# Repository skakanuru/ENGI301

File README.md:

<h1> ENGI301 </h1>
Repository for ENGI301 course work

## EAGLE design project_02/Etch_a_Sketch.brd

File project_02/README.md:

Project 2 for ENGI 301

Full PCB Design and Files for Etch-A-Sketch Design

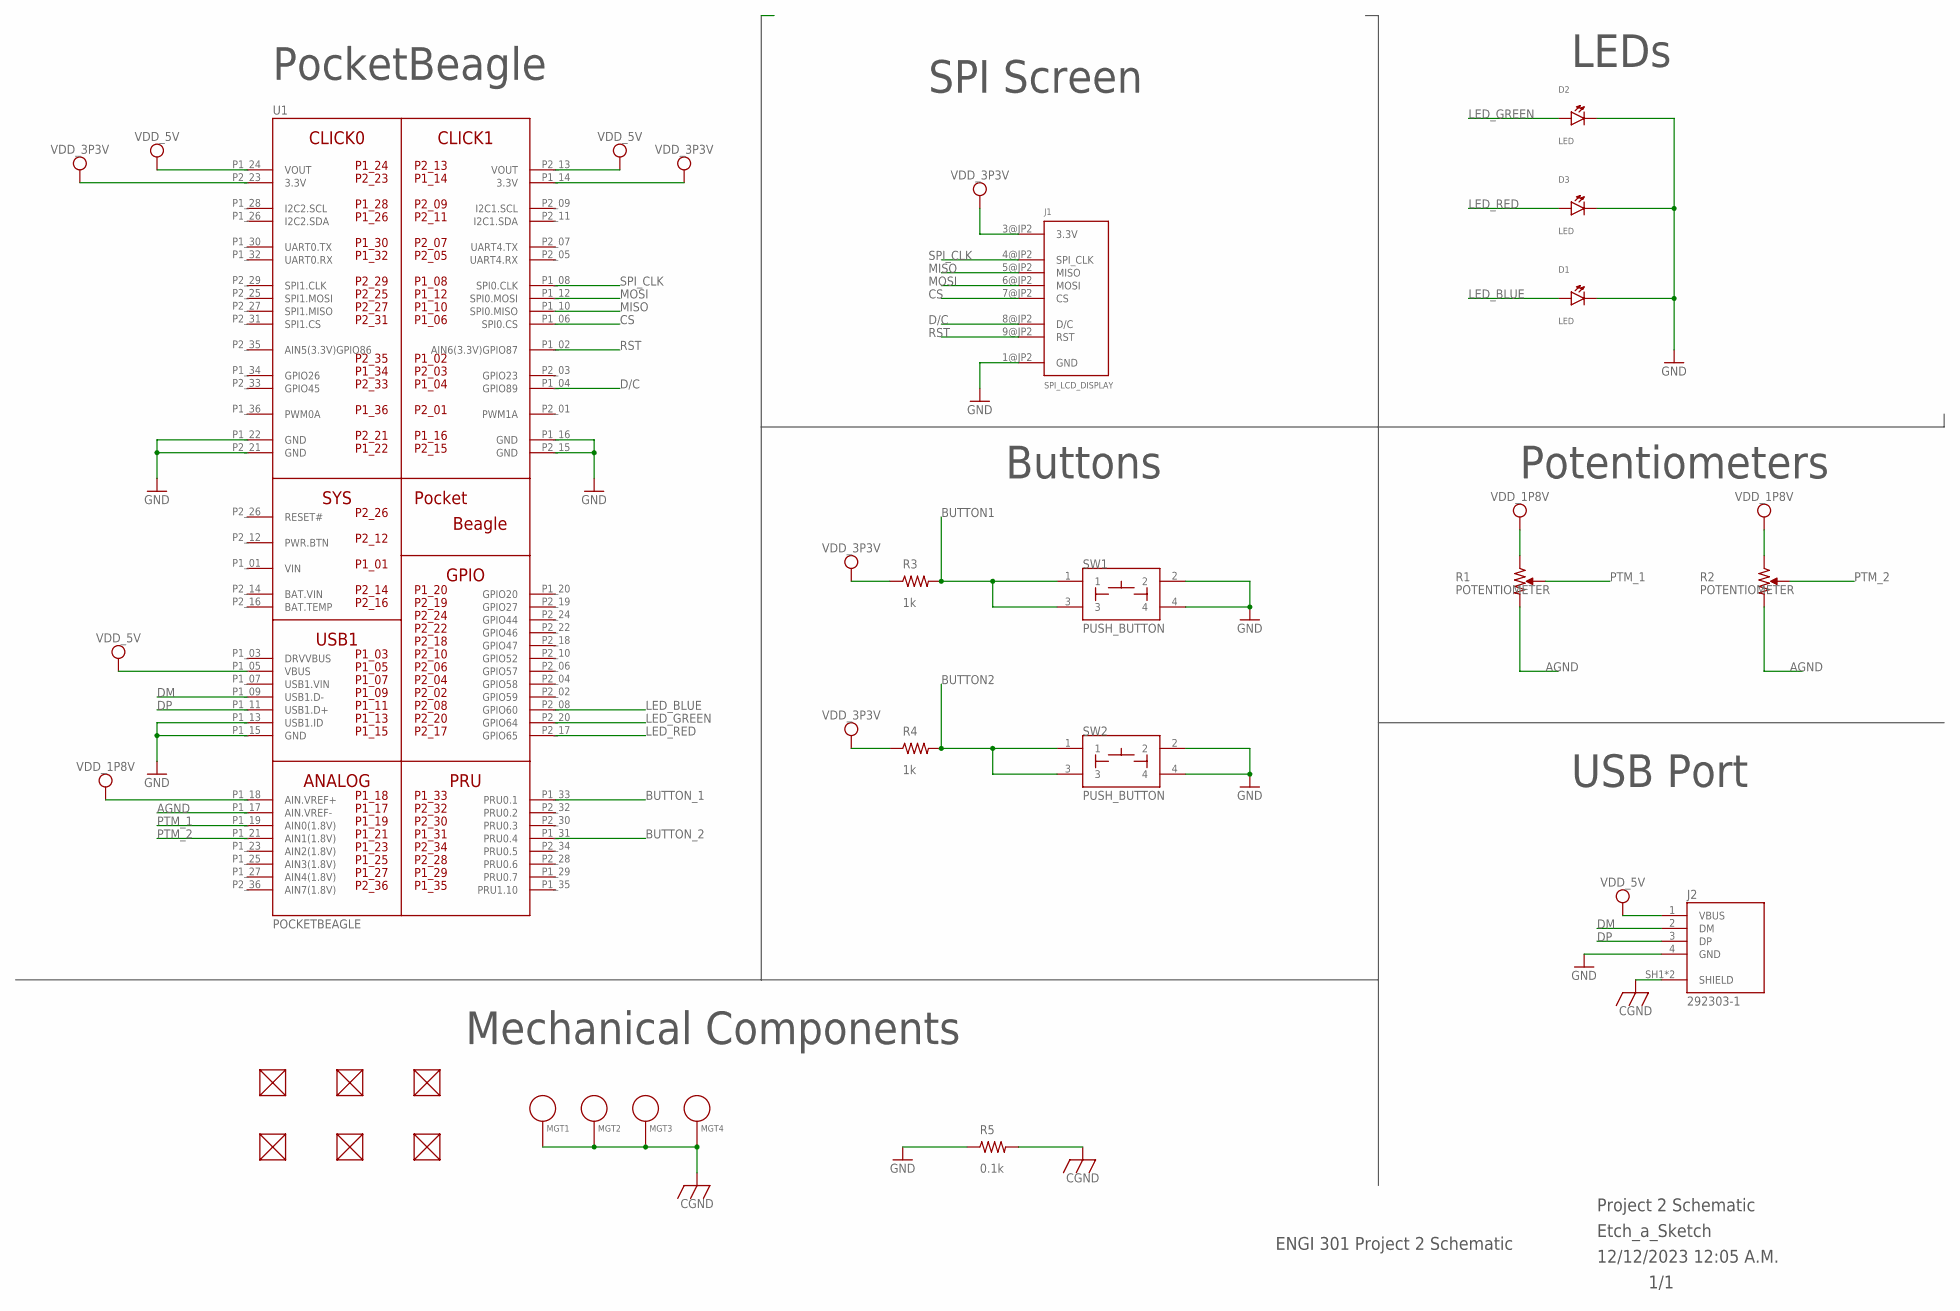
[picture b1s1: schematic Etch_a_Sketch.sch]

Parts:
D1, D2, D3: LED; EIA-STD
FUD1, FUD2, FUD3, FUD4, FUD5, FUD6: FIDUCIAL; FIDUCIAL_40MIL
J1: SPI_LCD_DISPLAY
J2: 292303-1; TE_292303-1
MGT1, MGT2, MGT3, MGT4: MOUNTING_HOLE
R1, R2: POTENTIOMETER; POT-PO90S
R3, R4: 1k; R0603
R5: 0.1k; R0603
SW1, SW2: PUSH_BUTTON; BUTTON_12.5MM
U1: POCKETBEAGLE

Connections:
AGND: R1.CW, R2.CW, U1.P1_17 (AIN.VREF-)
BAT.VIN: U1.P2_14 (BAT.VIN)
BUTTON1: R3.2, SW1.1, SW1.3
BUTTON2: R4.2, SW2.1, SW2.3
BUTTON_1: U1.P1_33 (PRU0.1)
BUTTON_2: U1.P1_31 (PRU0.4)
CGND: J2.SH1 (SHIELD), J2.SH2 (SHIELD), MGT1.P$1, MGT2.P$1, MGT3.P$1, MGT4.P$1, R5.2
CS: J1.7@JP2 (CS), U1.P1_06 (SPI0.CS)
D/C: J1.8@JP2 (D/C), U1.P1_04 (GPIO89)
DM: J2.2 (DM), U1.P1_09 (USB1.D-)
DP: J2.3 (DP), U1.P1_11 (USB1.D+)
GND: D1.CATHODE, D2.CATHODE, D3.CATHODE, J1.1@JP2 (GND), J2.4 (GND), R5.1, SW1.2, SW1.4, SW2.2, SW2.4, U1.P1_13 (USB1.ID), U1.P1_15 (GND), U1.P1_16 (GND), U1.P1_22 (GND), U1.P2_15 (GND), U1.P2_21 (GND)
LED_BLUE: D1.ANODE, U1.P2_08 (GPIO60)
LED_GREEN: D2.ANODE, U1.P2_20 (GPIO64)
LED_RED: D3.ANODE, U1.P2_17 (GPIO65)
MISO: J1.5@JP2 (MISO), U1.P1_10 (SPI0.MISO)
MOSI: J1.6@JP2 (MOSI), U1.P1_12 (SPI0.MOSI)
PTM_1: R1.S, U1.P1_19 (AIN0(1.8V))
PTM_2: R2.S, U1.P1_21 (AIN1(1.8V))
RST: J1.9@JP2 (RST), U1.P1_02 (AIN6(3.3V)GPIO87)
SPI_CLK: J1.4@JP2 (SPI_CLK), U1.P1_08 (SPI0.CLK)
VDD_1P8V: R1.CCW, R2.CCW, U1.P1_18 (AIN.VREF+)
VDD_3P3V: J1.3@JP2 (3.3V), R3.1, R4.1, U1.P1_14 (3.3V), U1.P2_23 (3.3V)
VDD_5V: J2.1 (VBUS), U1.P1_05 (VBUS), U1.P1_24 (VOUT), U1.P2_13 (VOUT)
VIN: U1.P1_01 (VIN)

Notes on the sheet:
Buttons
Potentiometers
LEDs
USB Port
Mechanical Components
SPI Screen
PocketBeagle
ENGI 301 Project 2 Schematic
Project 2 Schematic
1/1
Etch_a_Sketch
12/12/2023 12:05 A.M.

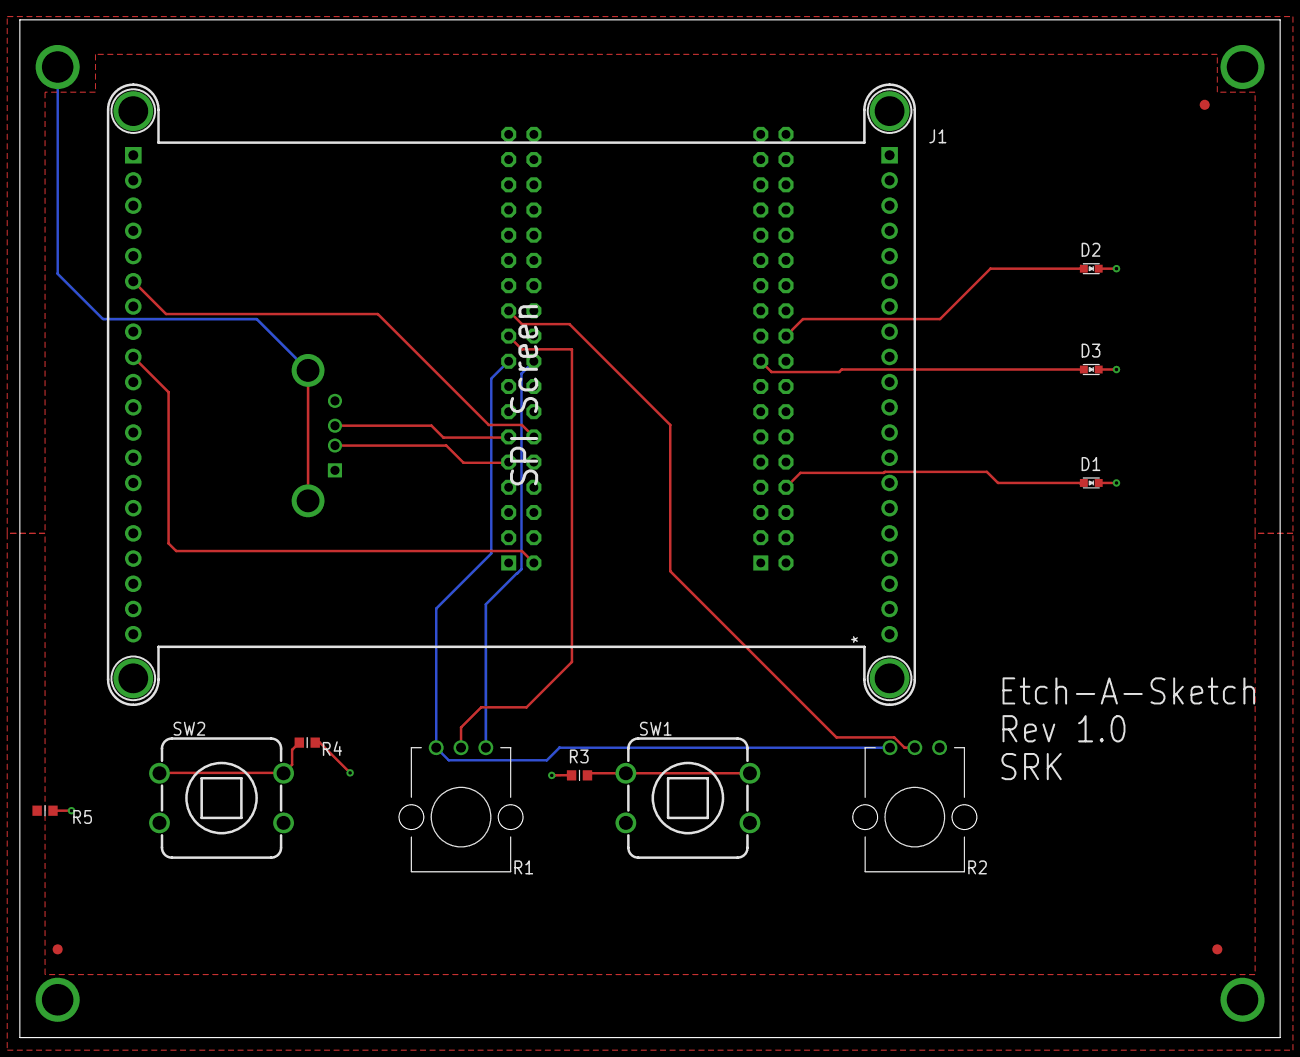
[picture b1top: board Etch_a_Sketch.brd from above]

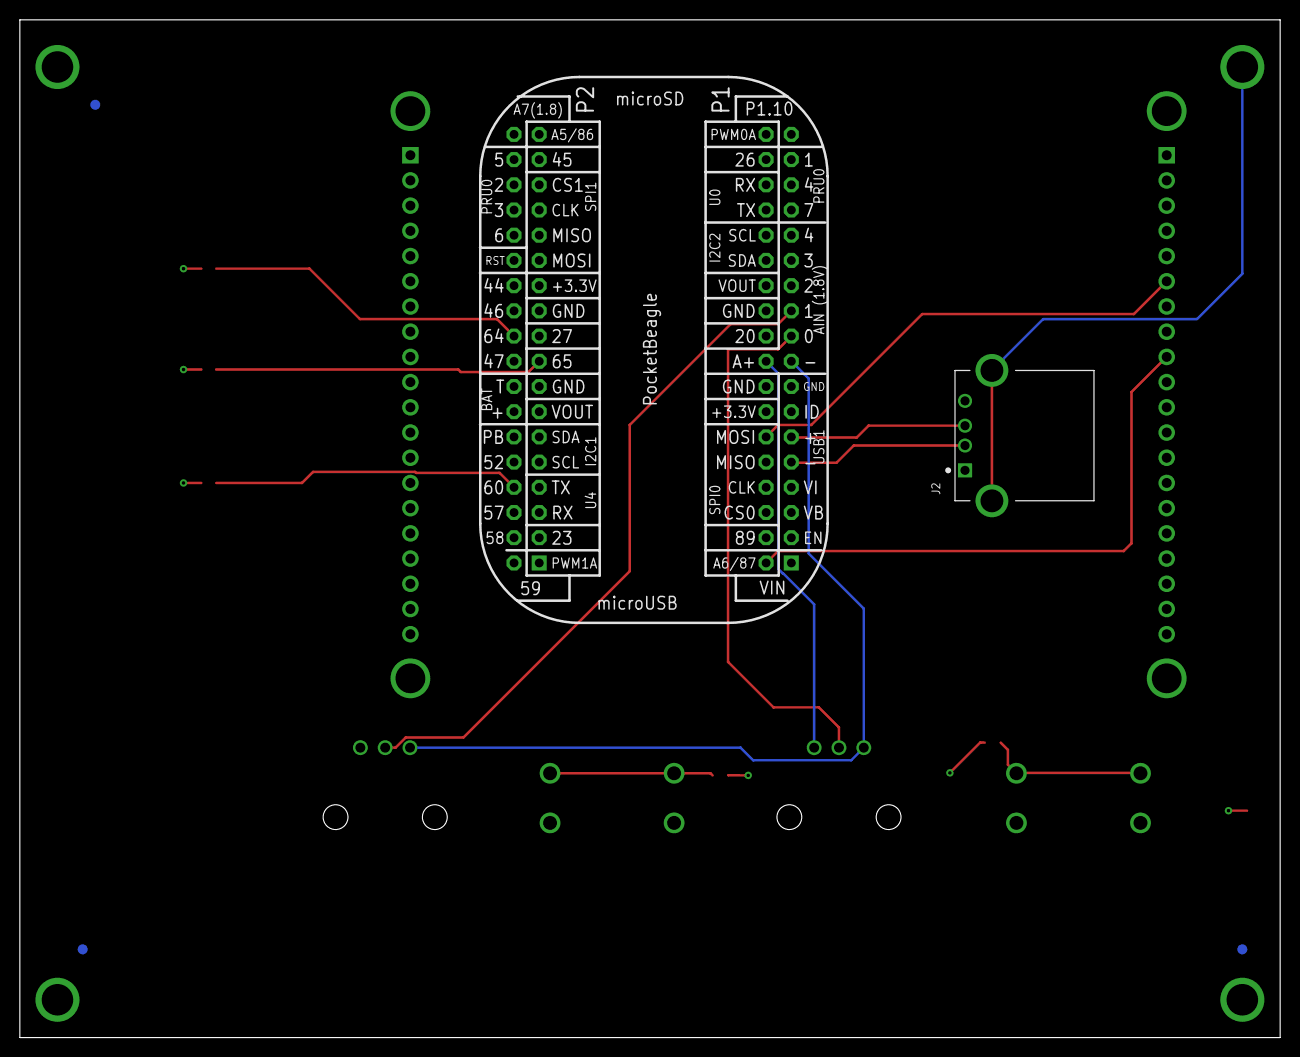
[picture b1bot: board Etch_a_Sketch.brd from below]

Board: 4 copper layers, 127.0 x 102.5 mm, 23 parts (5 on the bottom side), 21 nets.

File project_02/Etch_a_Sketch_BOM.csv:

"Qty";"Value";"Device";"Package";"Parts";"Description";"AVAILABILITY";"CENTERLINE_PITCH";"COMMENT";"DESCRIPTION";"EU_ROHS_COMPLIANCE";"MF";"MP";"NUMBER_OF_POSITIONS";"PACKAGE";"PRICE";"PRODUCT_TYPE";"PURCHASE-URL";
"1";"0.1k";"R_R0603";"R0603";"R5";"RESISTOR, American symbol";"";"";"";"";"";"";"";"";"";"";"";"";
"2";"1k";"R_R0603";"R0603";"R3, R4";"RESISTOR, American symbol";"";"";"";"";"";"";"";"";"";"";"";"";
"1";"292303-1";"292303-1";"TE_292303-1";"J2";"CONN USB RECEPT R/A TYPE A 4POS Check availability";"In Stock";"2 mm[.078 in]";"292303-1";" Conn";" Data";" USB";" Recept";" 2.0";" 4 Pos";" 1 Port";" Rt Angle";" A Ser";
"6";"FIDUCIAL";"FIDUCIAL";"FIDUCIAL_40MIL";"FUD1, FUD2, FUD3, FUD4, FUD5, FUD6";"";"";"";"";"";"";"";"";"";"";"";"";"";
"3";"LED";"LED";"EIA-STD";"D1, D2, D3";"EIA-STD LED, LTST-C191TBKT";"";"";"";"";"";"";"";"";"";"";"";"";
"4";"MOUNTING_HOLE";"MOUNTING_HOLE";"MOUNTING_HOLE";"MGT1, MGT2, MGT3, MGT4";"Chassis Mounting Hole w/GND connection ability";"";"";"";"";"";"";"";"";"";"";"";"";
"1";"POCKETBEAGLE";"POCKETBEAGLE";"POCKETBEAGLE";"U1";"";"";"";"";"";"";"";"";"";"";"";"";"";
"2";"POTENTIOMETER";"POTENTIOMETER";"POT-PO90S";"R1, R2";"Potentiometer - Examples:";"";"";"";"";"";"";"";"";"";"";"";"";
"2";"PUSH_BUTTON";"PUSH_BUTTON";"BUTTON_12.5MM";"SW1, SW2";"";"";"";"";"";"";"";"";"";"";"";"";"";
"1";"SPI_LCD_DISPLAY";"SPI_LCD_DISPLAY";"SPI_LCD_DISPLAY";"J1";"2.8" Adafruit SPI Display";"";"";"";"";"";"";"";"";"";"";"";"";

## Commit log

2023-09-26 Added right shift, left, exponentiation and modulus
2023-09-27 Problem 3 HW 4
2023-10-13 Create READ_ME
2023-10-13 Add files via upload
    Added software flow diagram.
2023-12-12 Create project_02
2023-12-12 Create ldkd
2023-12-12 Create idk
2023-12-12 Added files via upload
